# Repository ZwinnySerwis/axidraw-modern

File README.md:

# axidraw-modern

Współczesny kontroler plotera kompatybilny z oprogramowaniem [AxiDraw](https://github.com/evil-mad/axidraw): ten sam plugin Inkscape, ten sam protokół szeregowy EBB, nowa płyta z MCU i **gniazdami na stepsticki**.

## MVP

Host (Inkscape / CLI) zostaje jak w oryginale. Cała nowość siedzi w firmware, które udaje EiBotBoard:

1. USB CDC z nazwą produktu `EiBotBoard` (plugin szuka po nazwie, potem po VID/PID).
2. Odpowiedź na `V` zaczynająca się od `EBB` i zawierająca `Firmware Version 2.8.1`.
3. Kolejka ruchu: `SM`, `XM`, `SP`, `EM` → impulsy STEP/DIR na dwóch stepstickach + PWM serwa pióra.
4. Zapytania, których plugin naprawdę używa: `QP`, `QB`, `QS`, `QC`, `PI`, `QG`, `QL`/`SL`.

Kinematyka AxiDraw (mieszane osie / H-bot) liczy **host** i wysyła `XM` albo `SM`. Firmware nie musi znać geometrii ramienia — wykonuje dwa silniki w zadanym czasie.

## Układ repo

| Ścieżka | Co tam jest |
| --- | --- |
| `vendor/axidraw` | Upstream: plugin Inkscape, CLI, Python API |
| `vendor/EggBot` | Upstream: firmware EBB (PIC18) + HEX |
| `vendor/plotink` | Upstream: komunikacja USB/serial z EBB |
| `docs/` | Architektura, wybór MCU, protokół |
| `docs/upstream/` | Zrzuty schematów i dokumentacji EBB |
| `hardware/` | Pinout Pico ↔ stepstick, zasilanie |
| `firmware/` | Nasz firmware (RP2040 / Pico) |
| `host/` | Instalacja oryginalnego pluginu (MVP bez forka UI) |
| `tools/ebb_sim/` | Emulator protokołu EBB do testów bez sprzętu |
| `tests/` | Testy parsera |

## Szybki start (to środowisko)

```powershell
git clone --recurse-submodules https://github.com/ZwinnySerwis/axidraw-modern.git
cd axidraw-modern
python -m venv .venv
.\.venv\Scripts\Activate.ps1
pip install -r requirements-dev.txt
python -m pytest
```

Plugin Inkscape: zobacz [`host/README.md`](host/README.md). Firmware: [`firmware/README.md`](firmware/README.md). MCU: [`docs/MCU.md`](docs/MCU.md).

## Licencja

Oprogramowanie hosta AxiDraw / EggBot jest GPL-2.0. Ten repozytorium używa GPL-2.0 dla kodu pochodnego od pluginu. Nowy firmware w `firmware/` i emulator w `tools/` są na GPL-2.0, żeby nie mieszać licencji przy wspólnym drzewie.

Kod w `vendor/` należy do autorów upstream (Evil Mad Scientist / Bantam Tools / Schmalz Haus) i zostaje na ich licencjach.

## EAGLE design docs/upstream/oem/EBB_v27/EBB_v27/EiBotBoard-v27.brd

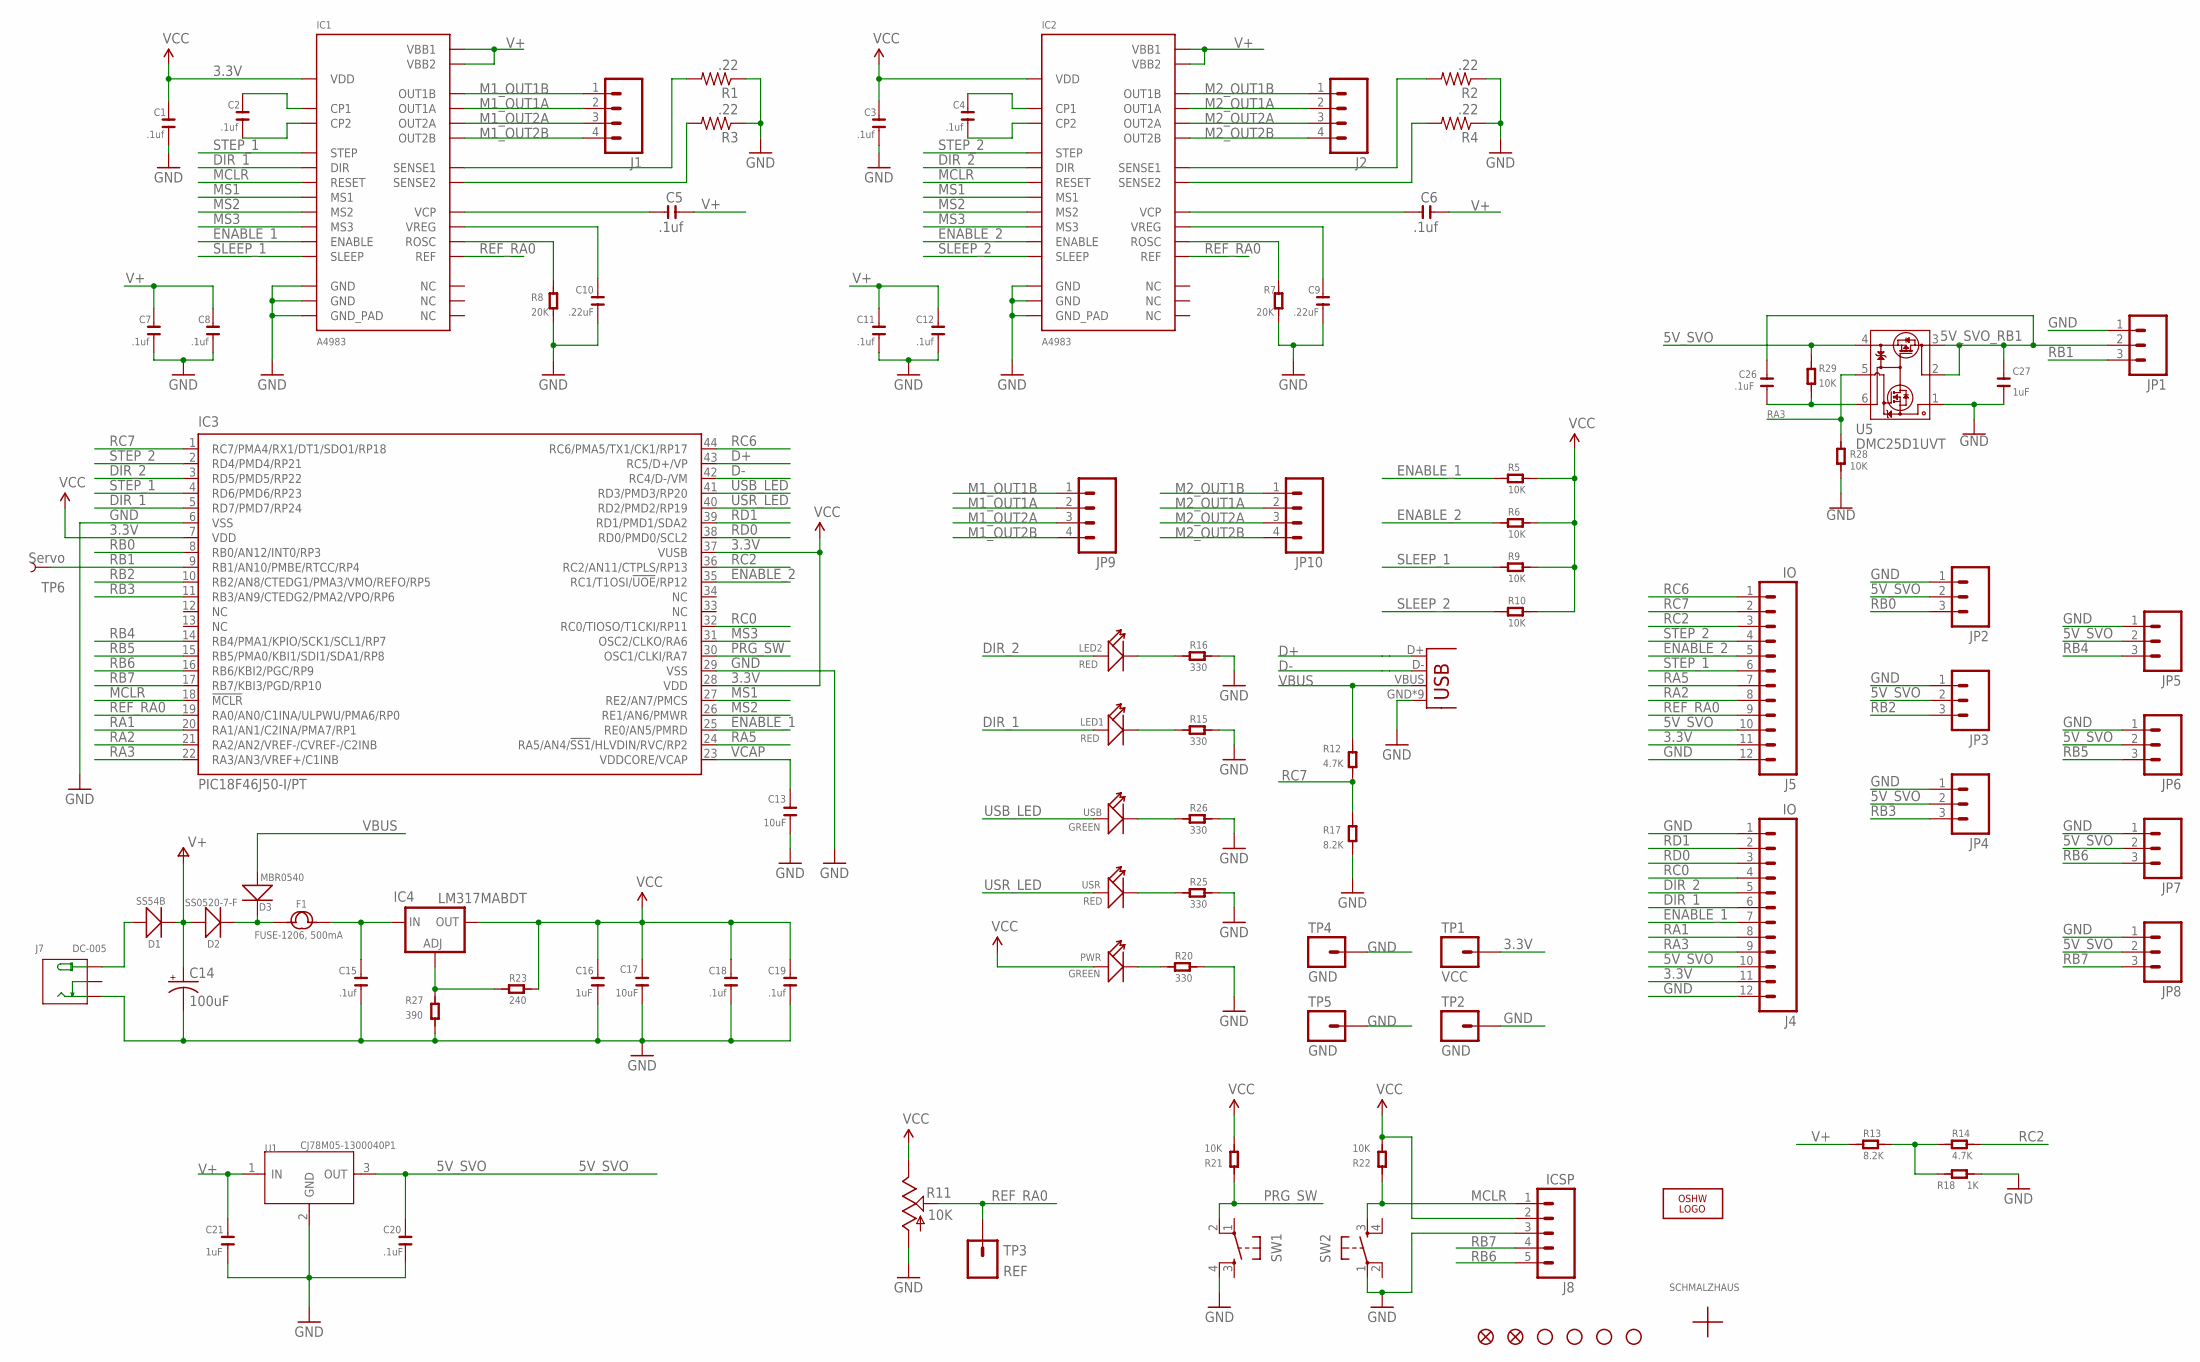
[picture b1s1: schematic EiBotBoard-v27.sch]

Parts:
C1, C2, C3, C4, C5, C6, C7, C8, C11, C12, C15, C18, C19: .1uf; C0603
C9, C10: .22uF; C0603
C13, C17: 10uF; C0805
C14: 100uF; PANASONIC_D
C16, C21, C27: 1uF; C0603
C20, C26: .1uF; C0603
D1: SS54B; SMB
D2: SS0520-7-F; SOD123
D3: MBR0540; SOD123
F1: FUSE-1206, 500mA; F1206
IC1, IC2: A4983; QFN28
IC3: PIC18F46J50-I/PT; TQFP44
IC4: LM317MABDT; DPACK
J1, J2: SCHMALZHAUS_M04; SCHMALZHAUS_SCREWTERMINAL-3.5MM-4_LOCK
J3: USBMICROB; USB-MICROB_FCI_PINS
J4, J5: IO; 1X12
J7: DC-005; DCJ3P-14.2X11.0X9.0MM
J8: ICSP; 1X05_NOSILK
JP1, JP2, JP3, JP4, JP5, JP6, JP7, JP8: M031X03_NO_SILK; 1X03_NO_SILK
JP9, JP10: M04POLAR; MOLEX-1X4
JP14, JP15: FIDUCIAL1X2; FIDUCIAL-1X2
LED1, LED2: RED; LED0603
LOGO1: OSHW_LOGO_8MILX0100-NT; OSHW_8X100_NOTEXT
PWR: GREEN; LED0603
R1, R2, R3, R4: .22; R0805
R5, R6, R9, R10, R21, R22, R28, R29: 10K; R0603
R7, R8: 20K; R0603
R11: 10K; 3MM_GENERIC_TRIMMER_POT
R12, R14: 4.7K; R0603
R13, R17: 8.2K; R0603
R15, R16, R20, R25, R26: 330; R0603
R18: 1K; R0603
R23: 240; R0603
R27: 390; R0603
SW1: PRG; TACTILE_SWITCH_SMD
SW2: RST; TACTILE_SWITCH_SMD
TP1: VCC; 1X01_NOSILK
TP2, TP4, TP5: GND; 1X01_NOSILK
TP3: REF; 1X01
TP6: Servo; PAD.03X.05
U1: CJ78M05-1300040P1; TO252
U5: DMC25D1UVT; TSOT26
U$1: SCHMALZHAUSSCHMALZHAUS_SMALL; SCHMALZHAUS_SMALL
U$2, U$3, U$4, U$5: STAND-OFF
USB: GREEN; LED0603
USR: RED; LED0603

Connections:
3.3V: C1.1, C3.1, C16.2, C17.2, C18.2, C19.2, IC1.P$15 (VDD), IC2.P$15 (VDD), IC3.7 (VDD), IC3.28 (VDD), IC3.37 (VUSB), IC4.4 (OUT), J4.11, J5.11, J8.2, PWR.+, R5.1, R6.1, R9.1, R10.1, R11.1 (E), R21.2, R22.2, R23.2, TP1.1
5V_SVO: C20.2, J4.10, J5.10, JP2.2, JP3.2, JP4.2, JP5.2, JP6.2, JP7.2, JP8.2, R29.1, U1.3 (OUT), U5.4 (VIN_R1)
5V_SVO_RB1: C26.1, C27.1, JP1.2, U5.2 (VOUT_C1$2), U5.3 (VOUT_C1$1)
D+: IC3.43 (RC5/D+/VP), J3.D+
D-: IC3.42 (RC4/D-/VM), J3.D-
DIR_1: IC1.P$19 (DIR), IC3.5 (RD7/PMD7/RP24), J4.6, LED1.+
DIR_2: IC2.P$19 (DIR), IC3.3 (RD5/PMD5/RP22), J4.5, LED2.+
ENABLE_1: IC1.P$2 (ENABLE), IC3.25 (RE0/AN5/PMRD), J4.7, R5.2
ENABLE_2: IC2.P$2 (ENABLE), IC3.35 (RC1/T1OSI/!UOE!/RP12), J5.5, R6.2
GND: C1.2, C3.2, C7.2, C8.2, C9.2, C10.2, C11.2, C12.2, C13.1, C14.-, C15.1, C16.1, C17.1, C18.1, C19.1, C20.1, C21.1, C27.2, IC1.P$3 (GND), IC1.P$18 (GND), IC1.P$29 (GND_PAD), IC2.P$3 (GND), IC2.P$18 (GND), IC2.P$29 (GND_PAD), IC3.6 (VSS), IC3.29 (VSS), J3.GND, J3.GND@1 (GND), J3.GND@2 (GND), J3.GND@3 (GND), J3.GND@4 (GND), J3.GND@5 (GND), J3.GND@6 (GND), J3.GND@7 (GND), J3.GND@8 (GND), J4.1, J4.12, J5.12, J7.P$2 (-), J8.3, JP1.1, JP2.1, JP3.1, JP4.1, JP5.1, JP6.1, JP7.1, JP8.1, R1.1, R2.1, R3.1, R4.1, R7.2, R8.2, R11.3 (A), R15.1, R16.1, R17.2, R18.2, R20.1, R25.1, R26.1, R27.2, R28.2, SW1.4, SW2.1, TP2.1, TP4.1, TP5.1, U1.2 (GND), U5.1 (R2)
M1_OUT1A: IC1.P$24 (OUT1A), J1.2, JP9.2
M1_OUT1B: IC1.P$21 (OUT1B), J1.1, JP9.1
M1_OUT2A: IC1.P$26 (OUT2A), J1.3, JP9.3
M1_OUT2B: IC1.P$1 (OUT2B), J1.4, JP9.4
M2_OUT1A: IC2.P$24 (OUT1A), J2.2, JP10.2
M2_OUT1B: IC2.P$21 (OUT1B), J2.1, JP10.1
M2_OUT2A: IC2.P$26 (OUT2A), J2.3, JP10.3
M2_OUT2B: IC2.P$1 (OUT2B), J2.4, JP10.4
MCLR: IC1.P$12 (RESET), IC2.P$12 (RESET), IC3.18 (!MCLR!), J8.1, R22.1, SW2.3
MS1: IC1.P$9 (MS1), IC2.P$9 (MS1), IC3.27 (RE2/AN7/PMCS)
MS2: IC1.P$10 (MS2), IC2.P$10 (MS2), IC3.26 (RE1/AN6/PMWR)
MS3: IC1.P$11 (MS3), IC2.P$11 (MS3), IC3.31 (OSC2/CLKO/RA6)
unnamed: LED2.-, R16.2
unnamed: D2.-, D3.-, F1.1
unnamed: C2.1, IC1.P$4 (CP1)
unnamed: R13.2, R14.1, R18.1
unnamed: C2.2, IC1.P$5 (CP2)
unnamed: D1.+, J7.P$1 (+)
unnamed: LED1.-, R15.2
unnamed: R26.2, USB.-
unnamed: IC4.1 (ADJ), R23.1, R27.1
unnamed: R25.2, USR.-
unnamed: PWR.-, R20.2
unnamed: C4.1, IC2.P$4 (CP1)
unnamed: C4.2, IC2.P$5 (CP2)
unnamed: IC1.P$13 (ROSC), R8.1
unnamed: C10.1, IC1.P$8 (VREG)
unnamed: C5.1, IC1.P$6 (VCP)
unnamed: IC1.P$27 (SENSE2), R3.2
unnamed: IC1.P$23 (SENSE1), R1.2
unnamed: C15.2, F1.2, IC4.3 (IN)
unnamed: C6.1, IC2.P$6 (VCP)
unnamed: IC2.P$23 (SENSE1), R2.2
unnamed: IC2.P$27 (SENSE2), R4.2
unnamed: C9.1, IC2.P$8 (VREG)
unnamed: IC2.P$13 (ROSC), R7.1
unnamed: C26.2, R29.2, U5.6 (R1_C1)
PRG_SW: IC3.30 (OSC1/CLKI/RA7), R21.1, SW1.2
RA1: IC3.20 (RA1/AN1/C2INA/PMA7/RP1), J4.8
RA2: IC3.21 (RA2/AN2/VREF-/CVREF-/C2INB), J5.8
RA3: IC3.22 (RA3/AN3/VREF+/C1INB), J4.9, R28.1, U5.5 (ON/OFF)
RA5: IC3.24 (RA5/AN4/!SS1!/HLVDIN/RVC/RP2), J5.7
RB0: IC3.8 (RB0/AN12/INT0/RP3), JP2.3
RB1: IC3.9 (RB1/AN10/PMBE/RTCC/RP4), JP1.3, TP6.P$1
RB2: IC3.10 (RB2/AN8/CTEDG1/PMA3/VMO/REFO/RP5), JP3.3
RB3: IC3.11 (RB3/AN9/CTEDG2/PMA2/VPO/RP6), JP4.3
RB4: IC3.14 (RB4/PMA1/KPIO/SCK1/SCL1/RP7), JP5.3
RB5: IC3.15 (RB5/PMA0/KBI1/SDI1/SDA1/RP8), JP6.3
RB6: IC3.16 (RB6/KBI2/PGC/RP9), J8.5, JP7.3
RB7: IC3.17 (RB7/KBI3/PGD/RP10), J8.4, JP8.3
RC0: IC3.32 (RC0/TIOSO/T1CKI/RP11), J4.4
RC2: IC3.36 (RC2/AN11/CTPLS/RP13), J5.3, R14.2
RC6: IC3.44 (RC6/PMA5/TX1/CK1/RP17), J5.1
RC7: IC3.1 (RC7/PMA4/RX1/DT1/SDO1/RP18), J5.2, R12.2, R17.1
RD0: IC3.38 (RD0/PMD0/SCL2), J4.3
RD1: IC3.39 (RD1/PMD1/SDA2), J4.2
REF_RA0: IC1.P$17 (REF), IC2.P$17 (REF), IC3.19 (RA0/AN0/C1INA/ULPWU/PMA6/RP0), J5.9, R11.2 (S), TP3.1
SLEEP_1: IC1.P$14 (SLEEP), R9.2
SLEEP_2: IC2.P$14 (SLEEP), R10.2
STEP_1: IC1.P$16 (STEP), IC3.4 (RD6/PMD6/RP23), J5.6
STEP_2: IC2.P$16 (STEP), IC3.2 (RD4/PMD4/RP21), J5.4
USB_LED: IC3.41 (RD3/PMD3/RP20), USB.+
USR_LED: IC3.40 (RD2/PMD2/RP19), USR.+
V+: C5.2, C6.2, C7.1, C8.1, C11.1, C12.1, C14.+, C21.2, D1.-, D2.+, IC1.P$22 (VBB1), IC1.P$28 (VBB2), IC2.P$22 (VBB1), IC2.P$28 (VBB2), R13.1, U1.1 (IN)
VBUS: D3.+, J3.VBUS, R12.1
VCAP: C13.2, IC3.23 (VDDCORE/VCAP)

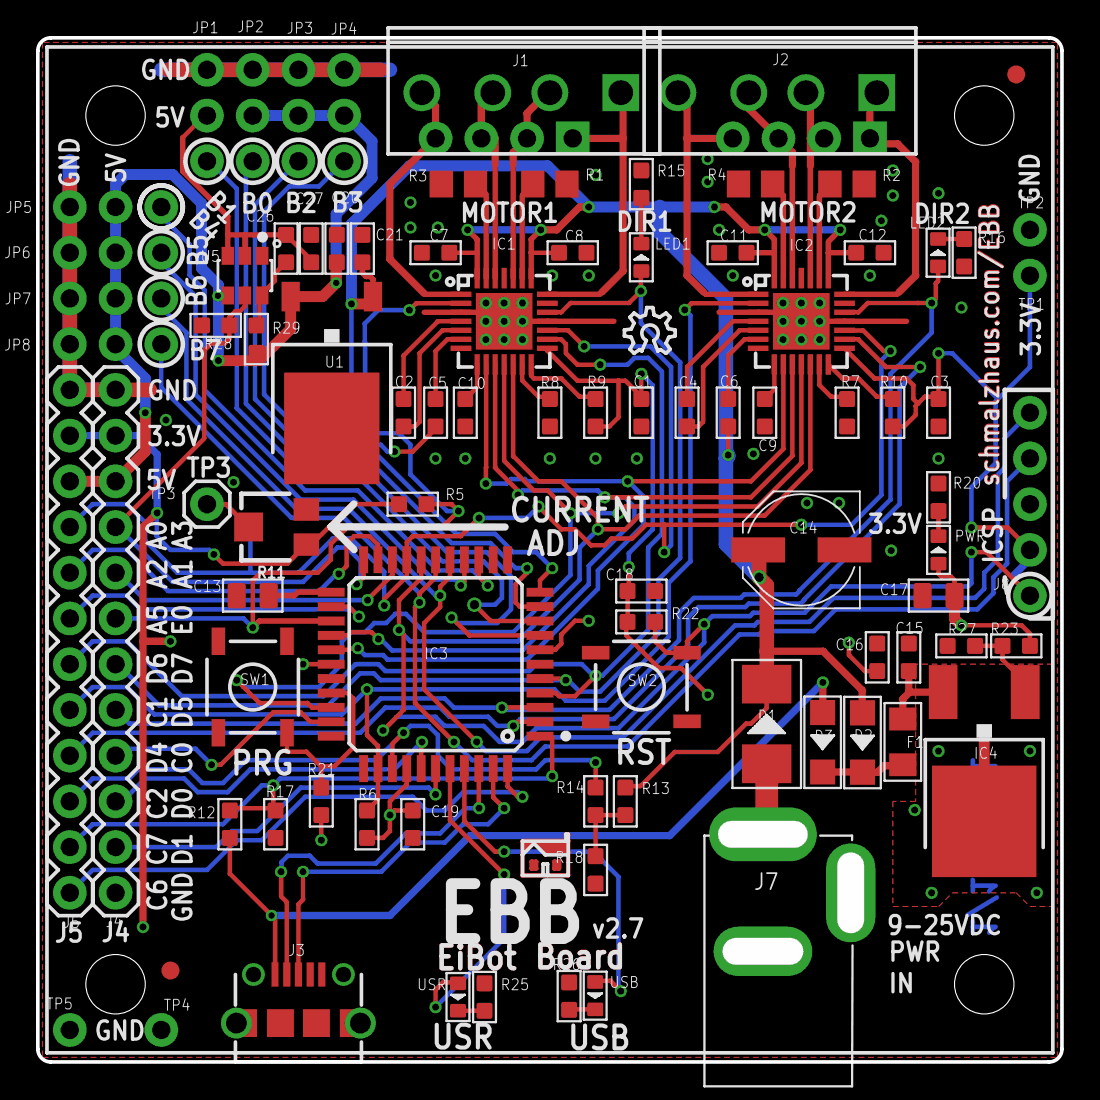
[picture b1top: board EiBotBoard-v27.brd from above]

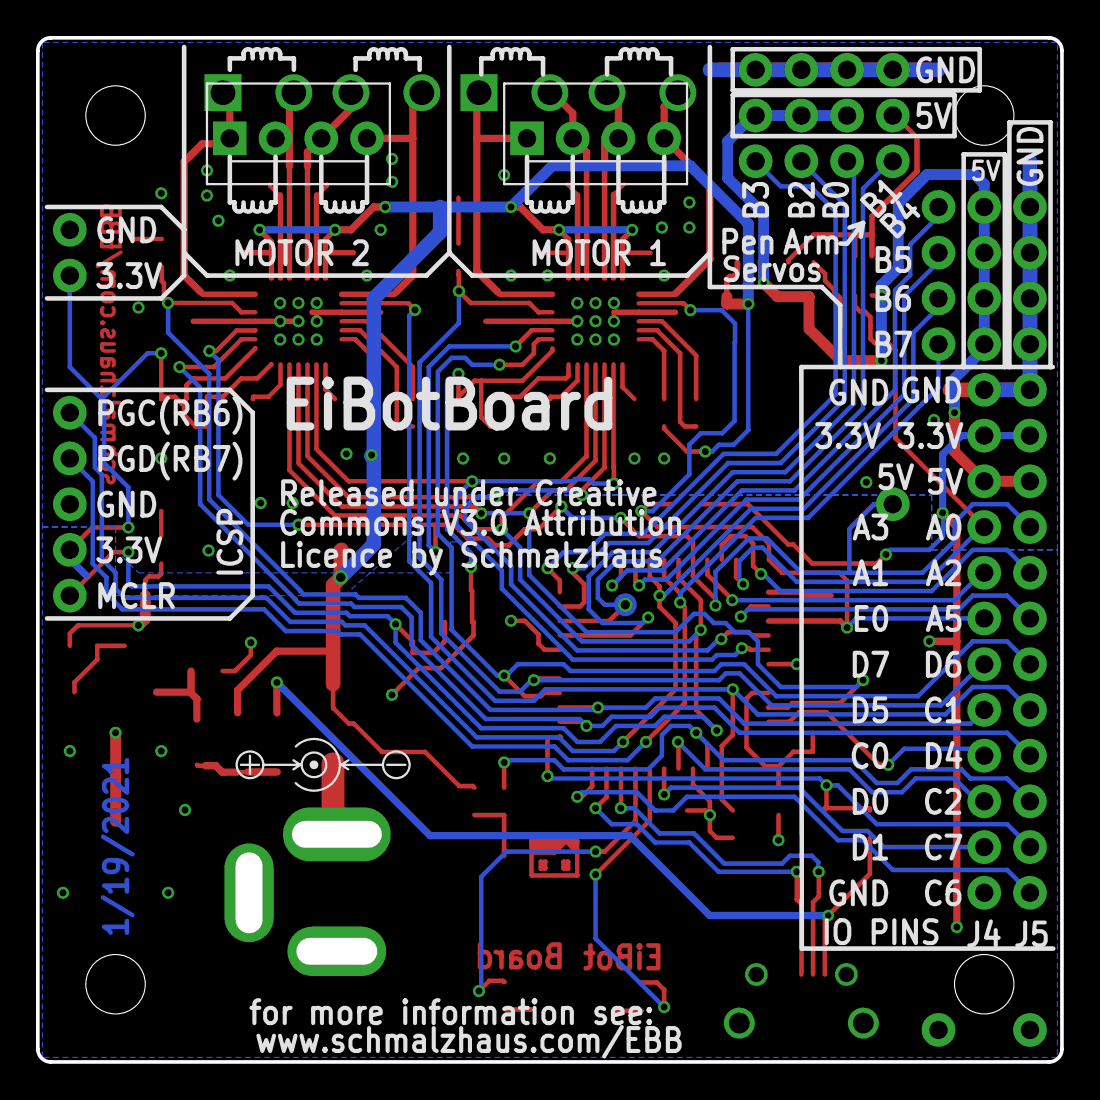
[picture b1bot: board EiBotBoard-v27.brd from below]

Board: 2 copper layers, 56.9 x 56.9 mm, 99 parts (3 on the bottom side), 76 nets.

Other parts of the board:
DRILEGEND: DRILEGEND

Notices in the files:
docs/upstream/oem/EBB_v27/EBB_v27/EiBotBoard-v27.brd:
Copyright 2021 Brian Schmalz Copyright and related rights are licensed under the Solderpad Hardware License, Version 2.1 (the "License");
Unless required by applicable law or agreed to in writing, software, hardware and materials distributed under this License is distributed on an
"AS IS" BASIS, WITHOUT WARRANTIES OR CONDITIONS OF ANY KIND, either express or implied. See the License for the specific language
docs/upstream/oem/EBB_v27/EBB_v27/EiBotBoard-v27.sch:
licenced under Creative Commons v3.0 Attribution licence
copyright 2011-2021
